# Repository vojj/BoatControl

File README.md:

# BoatControl
A raspberry pi project to control different ESC via an apple watch (Home Kit, Nest, ...)

## Warning
* This app is very new and only for testing
* Usage on your own risk

## Goals
- [x] Phase1: Control two or more propellers (0.6KW to 1.2KW)
- [x] Phase1: User want to controll speed via an apple watch
- [x] Phase1: Its working with WIFI
- [ ] Phase1: Its working with Bluetooth
- [ ] Phase2: Do control a bit more secure
- [ ] Phase3: GPS support (SpeedControl)

## System overview
* Raspberry Pi Zero W
* 2x ESC (PWM-Control Input)
* 2x Propellers
* Current und voltage measurement of battery circuit
* Fuses and Co.
* Battery (LifePo4)

# Software overview
* Homebridge and Homebridge MQTT (homebridge.io)
* MQTT Broker
* Python-APP with GUI (Calibration and control, MQTT Client)
> **pigpio** and uses a mock up class to do tests in windows env
> 
> paho.MQQT
* Node-RED flows (Setup MQTT)
* My apple watch or iPhone (Control (on, off, speed))

# Setup
## Install Raspberry Pi
* A lot of good guides you will find everywhere (https://www.raspberrypi.org)
* I am using Raspberry Pi OS with a standard image and belenaEtcher to write the SD-Card

## Install Homebridge and PlugINs
* Follow this Instructions: https://github.com/homebridge/homebridge/wiki/Install-Homebridge-on-Raspbian

## Install mosquitto broker via terminal
```
> sudo apt install mosquitto
> sudo apt install mosquitto-clients # if you need
> sudo systemctl enable mosquitto   # activate auto start
> TODO: Certification and account
```

## Install Node-RED
* https://nodered.org/docs/getting-started/raspberrypi (for a Raspberry Pi Zero you need an other install method)

## Install App
```
> git clone https://github.com/vojj/BoatControl.git
```

# Configuration
## Python-App
* Start manually or use autostart
* For the PWM-Output the pi using GPIO18 and GPIO13 (5V, GND directly from the Pi as well)
* !!! Please calibrate you ESC before usage !!!!

## Node-RED Flows and setup homebridge
* Please look into the wiki to see the Node-RED examples (https://github.com/vojj/BoatControl/wiki/Node-RED-Example).
```
> sudo systemctl enable nodered.service # Autostart Node-RED
```

## Raspberry Pi - GPIO
* Activate Remote GPIO (Raspberry Pi Configuration / Interfaces / Remote GPIO - Enable
```
> sudo pigpiod # start gpio domain, localhost
> sudo systemctl enable pigpiod # Autostart at boot
```

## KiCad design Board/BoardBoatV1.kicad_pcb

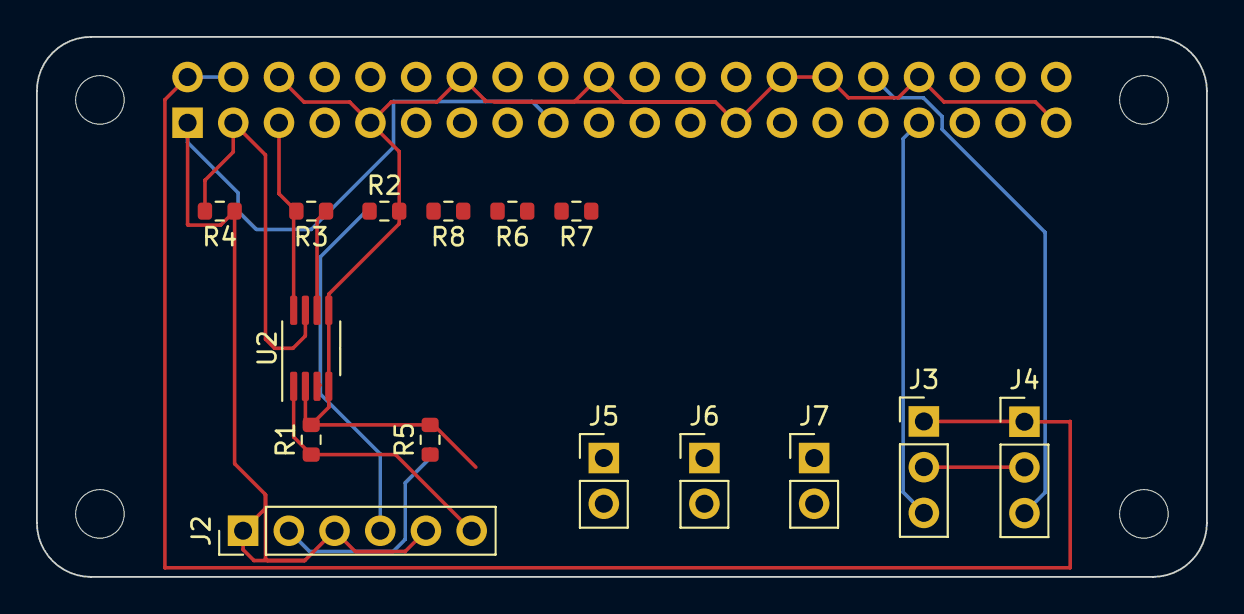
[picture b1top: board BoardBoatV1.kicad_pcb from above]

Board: 2 copper layers, 65.0 x 30.0 mm, 20 parts (1 on the bottom side), 13 nets.

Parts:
J1: GPIO; PinSocket_2x20_P2.54mm_Vertical
J2: Analog 1-3; PinHeader_1x06_P2.54mm_Vertical
J3: Motor1; PinHeader_1x03_P2.54mm_Vertical
J4: Motor2; PinHeader_1x03_P2.54mm_Vertical
J5: Switch1; PinHeader_1x02_P2.54mm_Vertical
J6: Switch2; PinHeader_1x02_P2.54mm_Vertical
J7: Switch3; PinHeader_1x02_P2.54mm_Vertical
MH1, MH2, MH3, MH4: MountingHole_2.7mm_M2.5
R1, R2, R5, R6, R7, R8: 10K; R_0603_1608Metric
R3: 5.0K; R_0603_1608Metric
R4: 5.0k; R_0603_1608Metric
U2: MCP3428; MSOP-8_3x3mm_P0.65mm

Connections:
+3V3: J1.1, J1.17, J2.1, J2.3, J2.5, J5.1, J6.1, J7.1, R3.1, R4.1, U2.6 (VDD)
+5V: J1.2, J1.4, J3.1, J4.1
/GPIO[17]: J1.11, J5.2, R6.1
/GPIO[22]: J1.15, J7.2, R8.1
/GPIO[27]: J1.13, J6.2, R7.1
GND: J1.6, J1.9, J1.14, J1.20, J1.25, J1.28, J1.30, J1.34, J1.39, J3.2, J4.2, R1.2, R2.2, R5.2, R6.2, R7.2, R8.2, U2.2 (CH1-), U2.4 (CH2-), U2.5 (VSS)
unnamed: J2.4, R2.1, U2.3 (CH2+)
unnamed: J2.6, R1.1, U2.1 (CH1+)
unnamed: J2.2, R5.1
PWM1: J1.33, J3.3
PWM2: J1.32, J4.3
SCL: J1.5, R3.2, U2.8 (SCL)
SDA: J1.3, R4.2, U2.7 (SDA)

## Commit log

2021-08-25 -working with apple watch
2021-08-27 add mqtt publish
2021-08-27 change format
2021-08-27 add sccale for motor speed
2021-08-29 add images for wiki
2021-08-29 Update issue templates
2021-09-01 Shutdown pi
2021-09-05 Add main switch
2021-09-05 add thread to esc softstop, init switch
2021-09-06 mock up for pigpio
2021-09-06 catch error while connecting
2021-09-06 add label for release status
2021-09-06 add enabled flag to esc
2021-09-06 add frames for status
2021-09-06 add async to mqtt client
2021-09-11 add runThread
2021-09-11 add on closing callback
2021-09-11 add label
2021-09-11 add event handler
2021-09-11 add dependencies
2021-09-11 add on quit
2021-09-12 event handler is now global
2021-09-12 change dep
2022-08-28 3 scwitches for speed
2022-08-28 added board
2022-08-28 gpio
